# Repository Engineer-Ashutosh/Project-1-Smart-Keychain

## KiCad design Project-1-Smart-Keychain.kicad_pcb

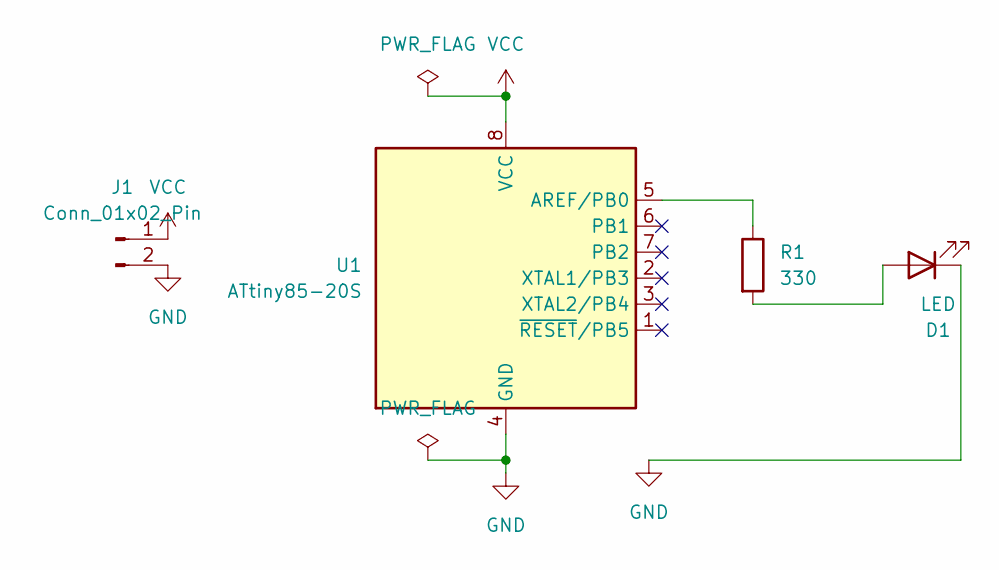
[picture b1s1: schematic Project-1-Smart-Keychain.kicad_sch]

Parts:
D1: LED; LED_D5.0mm_Clear
J1: Conn_01x02_Pin; PinHeader_1x02_P2.54mm_Vertical
R1: 330; R_Axial_DIN0207_L6.3mm_D2.5mm_P7.62mm_Horizontal
U1: ATtiny85-20S; CERDIP-8_W7.62mm_SideBrazed

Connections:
GND: D1.1 (K), J1.2, U1.4 (GND)
unnamed: D1.2 (A), R1.2
unnamed: R1.1, U1.5 (AREF/PB0)
VCC: J1.1, U1.8 (VCC)

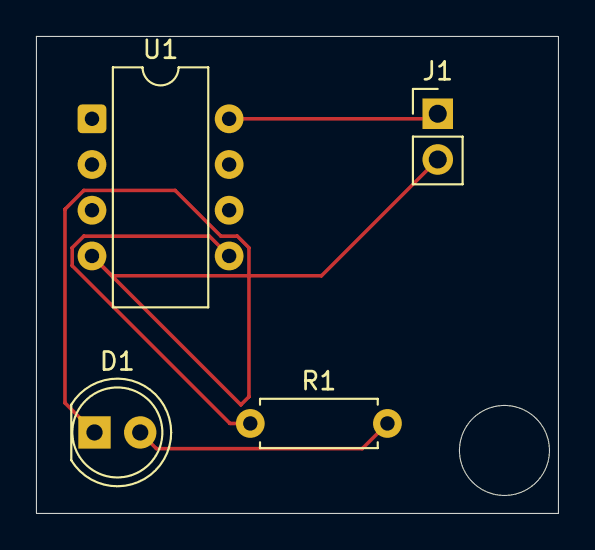
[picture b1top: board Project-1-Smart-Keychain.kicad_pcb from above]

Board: 2 copper layers, 29.0 x 26.5 mm, 4 parts (0 on the bottom side), 4 nets.
